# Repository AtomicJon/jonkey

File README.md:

# JONKEY

The JONKEY is a columnar split keyboard created using [ergogen](https://github.com/ergogen/ergogen).

## v2

#### What's New
- Swap thumb layout
- Added encoder mounts
- Added screen
- TODO: Touchpad mount

### Project Contents
- Ergogen Config: [jonkey-v2.yml](jonkey-v2.yml)
- PCB Design: [pcbs/](pcbs/)
- 3D Printable case: __TODO__
- QMK Config: [qmk_config/](qmk_config/)

## v1

### Project Contents
- Ergogen Config: [jonkey.yml](v1/jonkey.yml)
- PCB Design: [v1/pcbs/v1.1/](v1/pcbs/v1.1/)
- 3D Printable case: [case/](v1/case/)
  - The newest version has a 5 degree slope and tighter tolerances
    - [Left](v1/case/Case%20-%20Left%20-%205deg.stl)
    - [Right](v1/case/Case%20-%20Right%20-%205deg.stl)
- QMK Config: [qmk_config/](v1/qmk_config/)

## Notes
- The PCB is a single reversible board, flip it over for the right side
- The Pro Micros need to be attached upside down on the left and right side up on the right for the correct pin alignments
- Currently the QMK firmware has the side hardcoded and needs to be complied individually for each side. To switch between compiling the left/right side firmware, uncomment the appropriate line in the [config.h](v1/qmk_config/atomicjon/jonkey/config.h) (Lines 16/17)
  - There are free pins (D2, D3) that could be used for high/low indication of side

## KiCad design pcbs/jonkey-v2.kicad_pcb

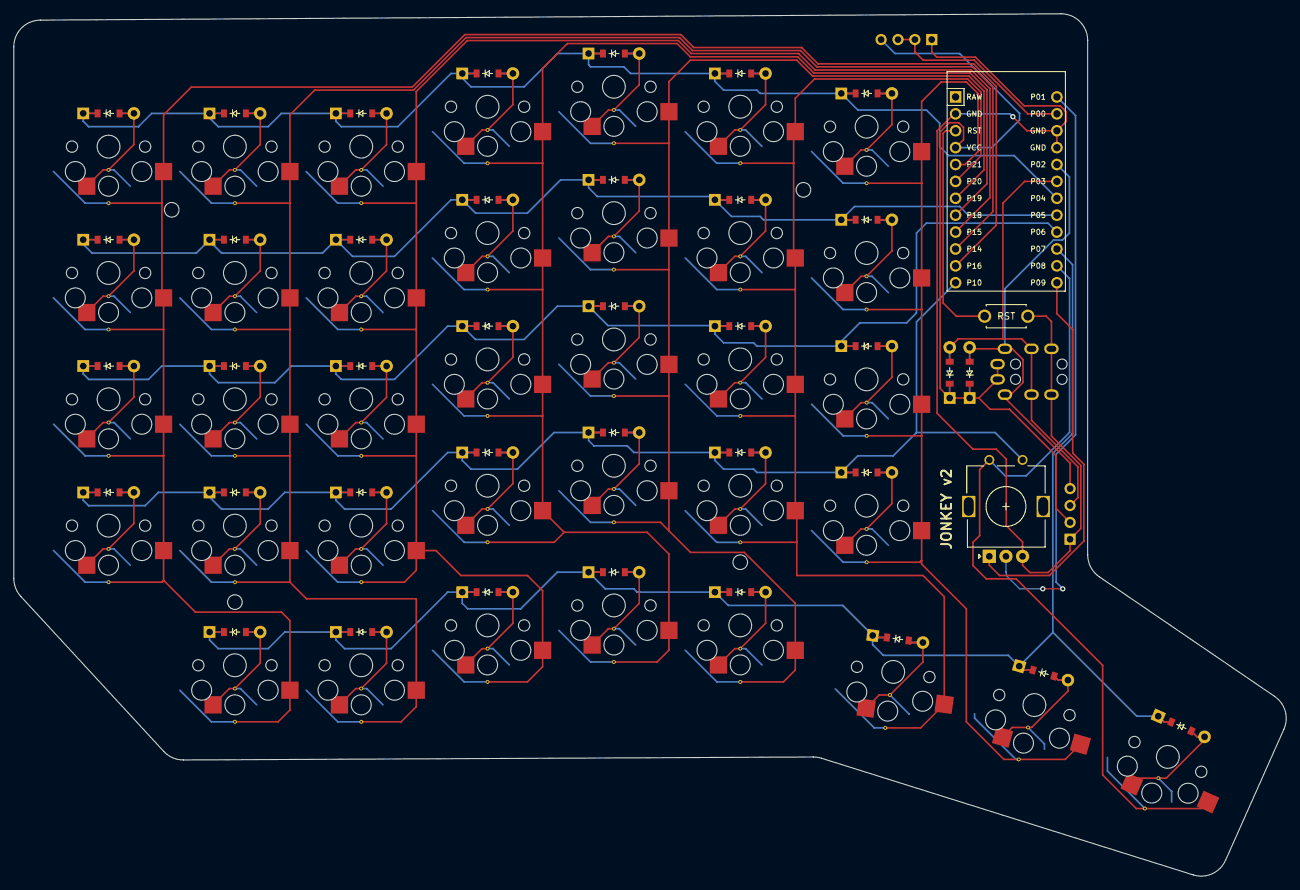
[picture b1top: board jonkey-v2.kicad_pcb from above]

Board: 2 copper layers, 191.4 x 129.7 mm, 84 parts (0 on the bottom side), 57 nets.

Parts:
D1, D2, D3, D4, D5, D6, D7, D8, D9, D10, D11, D12, D13, D14, D15, D16, D17, D18, D19, D20, D21, D22, D23, D24, D25, D26, D27, D28, D29, D30, D31, D32, D33, D34, D35, D36: ComboDiode
MCU1: ProMicro
MH1, MH2, MH3, MH4: mounting_hole_npth
OLED1: OLED; OLED_headers
R11, R21: ComboDiode
ROT1: rotary_encoder
RST1: reset_switch_tht_top
S1, S2, S3, S4, S5, S6, S7, S8, S9, S10, S11, S12, S13, S14, S15, S16, S17, S18, S19, S20, S21, S22, S23, S24, S25, S26, S27, S28, S29, S30, S31, S32, S33, S34, S35, S36: PG1350
SERIAL1: SERIAL; OLED_headers
TRRS1: TRRS-PJ-320A-dual

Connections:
GND: MCU1.2, MCU1.15, MCU1.16, OLED1.1, ROT1.B, RST1.1, SERIAL1.1, TRRS1.4
P0: MCU1.14, SERIAL1.2, SERIAL1.3
P1: MCU1.13, ROT1.C
P2: MCU1.17, OLED1.4, R21.2, TRRS1.2
P3: MCU1.18, OLED1.3, R11.2, TRRS1.3
P4: D4.1, D9.1, D14.1, D19.1, D24.1, D29.1, D33.1, MCU1.19
P5: D3.1, D8.1, D13.1, D18.1, D23.1, D28.1, D32.1, MCU1.20
P6: D2.1, D7.1, D12.1, D17.1, D22.1, D27.1, D31.1, MCU1.21
P7: D5.1, D10.1, D15.1, D20.1, D25.1, D34.1, D35.1, D36.1, MCU1.22
P8: MCU1.23, ROT1.1, S36.2
P9: MCU1.24, ROT1.A
P10: D1.1, D6.1, D11.1, D16.1, D21.1, D26.1, D30.1, MCU1.12, ROT1.2
P14: MCU1.10, S6.2, S7.2, S8.2, S9.2, S10.2
P15: MCU1.9, S11.2, S12.2, S13.2, S14.2, S15.2
P16: MCU1.11, S1.2, S2.2, S3.2, S4.2, S5.2
P18: MCU1.8, S16.2, S17.2, S18.2, S19.2, S20.2
P19: MCU1.7, S21.2, S22.2, S23.2, S24.2, S25.2
P20: MCU1.6, S26.2, S27.2, S28.2, S29.2, S34.2
P21: MCU1.5, S30.2, S31.2, S32.2, S33.2, S35.2
RST: MCU1.3, RST1.2
VCC: MCU1.4, OLED1.2, R11.1, R21.1, SERIAL1.4, TRRS1.1
index_bottom: D26.2, S26.1
index_home: D27.2, S27.1
index_modifiers: D25.2, S25.1
index_numbers: D29.2, S29.1
index_top: D28.2, S28.1
inner1_bottom: D30.2, S30.1
inner1_home: D31.2, S31.1
inner1_numbers: D33.2, S33.1
inner1_thumbrow: D34.2, S34.1
inner1_top: D32.2, S32.1
middle_bottom: D21.2, S21.1
middle_home: D22.2, S22.1
middle_modifiers: D20.2, S20.1
middle_numbers: D24.2, S24.1
middle_top: D23.2, S23.1
outer1_bottom: D6.2, S6.1
outer1_home: D7.2, S7.1
outer1_modifiers: D5.2, S5.1
outer1_numbers: D9.2, S9.1
outer1_top: D8.2, S8.1
outer2_bottom: D1.2, S1.1
outer2_home: D2.2, S2.1
outer2_numbers: D4.2, S4.1
outer2_top: D3.2, S3.1
pinky_bottom: D11.2, S11.1
pinky_home: D12.2, S12.1
pinky_modifiers: D10.2, S10.1
pinky_numbers: D14.2, S14.1
pinky_top: D13.2, S13.1
ring_bottom: D16.2, S16.1
ring_home: D17.2, S17.1
ring_modifiers: D15.2, S15.1
ring_numbers: D19.2, S19.1
ring_top: D18.2, S18.1
thumb1_thumbrow: D35.2, S35.1
thumb2_thumbrow: D36.2, S36.1

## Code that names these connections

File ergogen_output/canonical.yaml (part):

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    autobind: 10
    skip: false
    asym: both
    colrow: pinky_modifiers
    name: matrix_pinky_modifiers
    column_net: P14
    row_net: P7
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    autobind: 10
    skip: false
    asym: both
    colrow: pinky_bottom
    name: matrix_pinky_bottom
    column_net: P15
    row_net: P10
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    autobind: 10
    skip: false
    asym: both
    colrow: pinky_home
    name: matrix_pinky_home
    column_net: P15
    row_net: P6
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    autobind: 10
    skip: false
    asym: both
    colrow: pinky_top
    name: matrix_pinky_top
    column_net: P15
    row_net: P5
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    autobind: 10
    skip: false
    asym: both
    colrow: pinky_numbers
    name: matrix_pinky_numbers
    column_net: P15
    row_net: P4
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
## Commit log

2022-03-08 Check in v1 files
2023-01-28 Add comment regarding switching to I2C
    The board is wired for either serial or I2C for communication between sides. Currently serial is used, but I2C can be used by adding a pullup resistor between pins D0 and D1, commenting out `SOFT_SER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
2023-05-08 Update to latest version of QMK and latest keymap
2024-06-11 Add new cases with slope and tighter tolerances
2024-06-11 Update images
2024-11-17 feat(ergogen): update ergogen config to work with new v4 format
2024-11-17 feat(pcb): check in v1.1
2024-11-18 feat(v2): move v1 and add initial config for v2
2024-11-18 fix(readme): update links in README with reorg
2024-11-21 feat: add a few mounting holds, increase thumb distance, increase stagger beyound pinky
2024-11-21 feat: add place for pull up resistors for i2c
2024-11-24 feat: shift thumb column pins to free up 1 pin
2024-11-24 feat: free up pin 0 incase its needed for serial coms and add access via 4 pins
2024-11-25 feat: routing done + switch P2 and P3 resistor placement for easier routing
2024-12-14 feat: check in latest PCBs (wrong pins for encoder)
2025-01-03 feat: check in first pass of v2 qmk config
2025-02-11 chore: update README with v2 details
2025-10-22 feat: check in v2 case files
